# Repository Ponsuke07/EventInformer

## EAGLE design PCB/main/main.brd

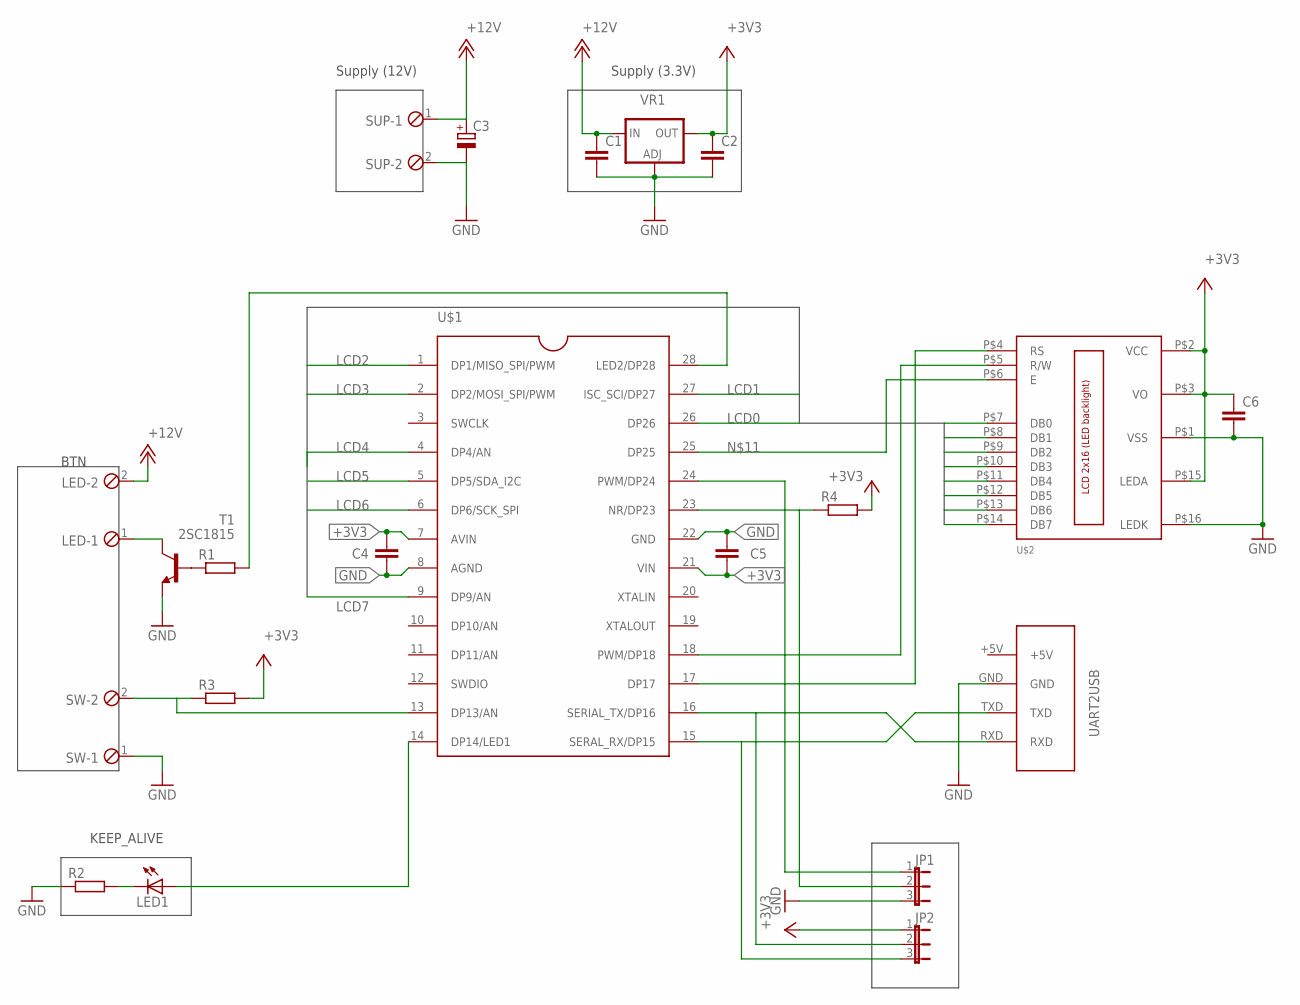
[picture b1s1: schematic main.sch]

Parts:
C1, C4, C5, C6: C-EUC2012; C2012
C2: C-EUC3216; C3216
C3: CPOL-EUE2-5; E2-5
JP1, JP2: JP2E; JP2
LED: MPT2; 2POL254
LED1: LED3MM
R1: R-EU_0207/10; 0207/10
R2, R4: R-EU_R2012; R2012
R3: R-EU_0204/7; 0204/7
SUP: MPT2; 2POL254
SW: MPT2; 2POL254
T1: 2SC1815; TO92-ECB
U$1: LPC1114FDH28; TSSOP28
U$2: LCD_2X16_CON2; 16X1_DIP
UART2USB: USB2UART
VR1: LD117ADT33TR; DPACK

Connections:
+3V3: C2.1, C4.1, C5.2, C6.1, JP2.1, R3.2, R4.2, U$1.7 (AVIN), U$1.21 (VIN), U$2.P$2 (VCC), U$2.P$3 (VO), U$2.P$15 (LEDA), VR1.4 (OUT)
+12V: C1.1, C3.+, LED.2, SUP.1, VR1.3 (IN)
GND: C1.2, C2.2, C3.-, C4.2, C5.1, C6.2, JP1.3, R2.1, SUP.2, SW.1, T1.E, U$1.8 (AGND), U$1.22 (GND), U$2.P$1 (VSS), U$2.P$16 (LEDK), UART2USB.GND, VR1.1 (ADJ)
LCD0: U$1.26 (DP26), U$2.P$7 (DB0)
LCD1: U$1.27 (ISC_SCI/DP27), U$2.P$8 (DB1)
LCD2: U$1.1 (DP1/MISO_SPI/PWM), U$2.P$9 (DB2)
LCD3: U$1.2 (DP2/MOSI_SPI/PWM), U$2.P$10 (DB3)
LCD4: U$1.4 (DP4/AN), U$2.P$11 (DB4)
LCD5: U$1.5 (DP5/SDA_I2C), U$2.P$12 (DB5)
LCD6: U$1.6 (DP6/SCK_SPI), U$2.P$13 (DB6)
LCD7: U$1.9 (DP9/AN), U$2.P$14 (DB7)
unnamed: R3.1, SW.2, U$1.13 (DP13/AN)
unnamed: JP2.3, U$1.15 (SERAL_RX/DP15), UART2USB.TXD
unnamed: JP2.2, U$1.16 (SERIAL_TX/DP16), UART2USB.RXD
unnamed: LED1.A, U$1.14 (DP14/LED1)
unnamed: LED.1, T1.C
unnamed: R1.1, T1.B
unnamed: LED1.K (C), R2.2
unnamed: R1.2, U$1.28 (LED2/DP28)
unnamed: JP1.2, R4.1, U$1.23 (NR/DP23)
unnamed: JP1.1, U$1.24 (PWM/DP24)
unnamed: U$1.25 (DP25), U$2.P$6 (E)
unnamed: U$1.18 (PWM/DP18), U$2.P$5 (R/W)
unnamed: U$1.17 (DP17), U$2.P$4 (RS)

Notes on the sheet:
Supply (12V)
Supply (3.3V)
BTN
KEEP_ALIVE

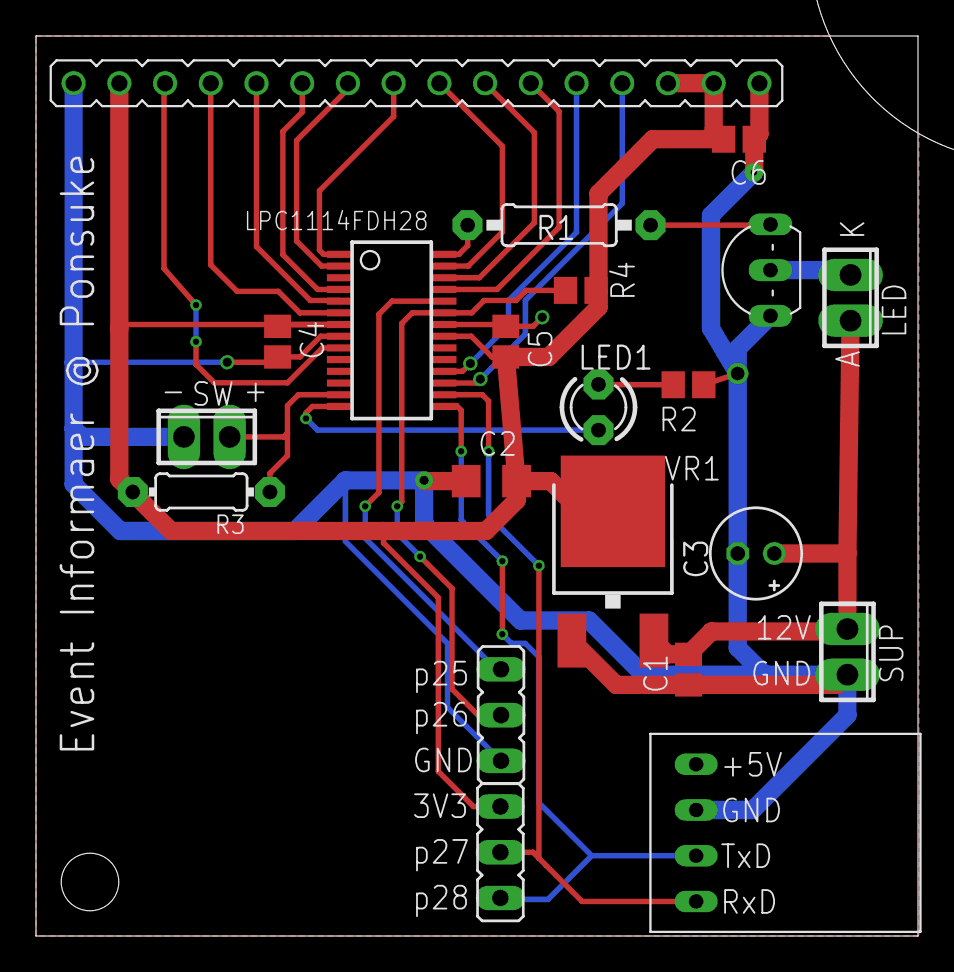
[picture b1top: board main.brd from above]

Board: 2 copper layers, 49.0 x 50.0 mm, 21 parts (0 on the bottom side), 24 nets.

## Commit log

2018-02-14 Add 3D model to use as the button and PCB case.
2018-02-24 model: Update scad modle.
2018-04-01 PCB: Add main.{brd,sch}.
2018-04-01 src: Just start as copy sample code of google calender api.
2018-04-01 PCB: lib: Add eagle libs.
    List of libraries witch are added is below.
    * TWELite
    * aquest
    * com-phoenix-254
    * lpc1114fn28
2018-04-01 gitignore: Add git ignore.
    Add ignore lists for eagle(PCB tool), C++, python.
2018-04-01 doc: Add pin assign list.
2018-04-09 PCB: Add DIP con for programing writer like isp writer.
    Note that the pin assignment was modified because "reset" and"ISP Enable"
    pins are required by "ISP writer" but they were used for LCD.
2018-04-09 PCB: lib: Add 2x16 lcd library.
2018-08-12 model: Add a support for PCB.
